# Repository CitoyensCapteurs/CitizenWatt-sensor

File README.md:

CitizenWatt-sensor
==================
Hardware and code running on the sensor for the CitizenWatt project.

For the sensor, install some libs first :
- RF24: https://github.com/stanleyseow/RF24/tree/2a1a4e6e27056844a3bc419d65b8a2d4e0f1770e
- EmonLib: https://github.com/openenergymonitor/EmonLib
- AESLib: https://github.com/DavyLandman/AESLib

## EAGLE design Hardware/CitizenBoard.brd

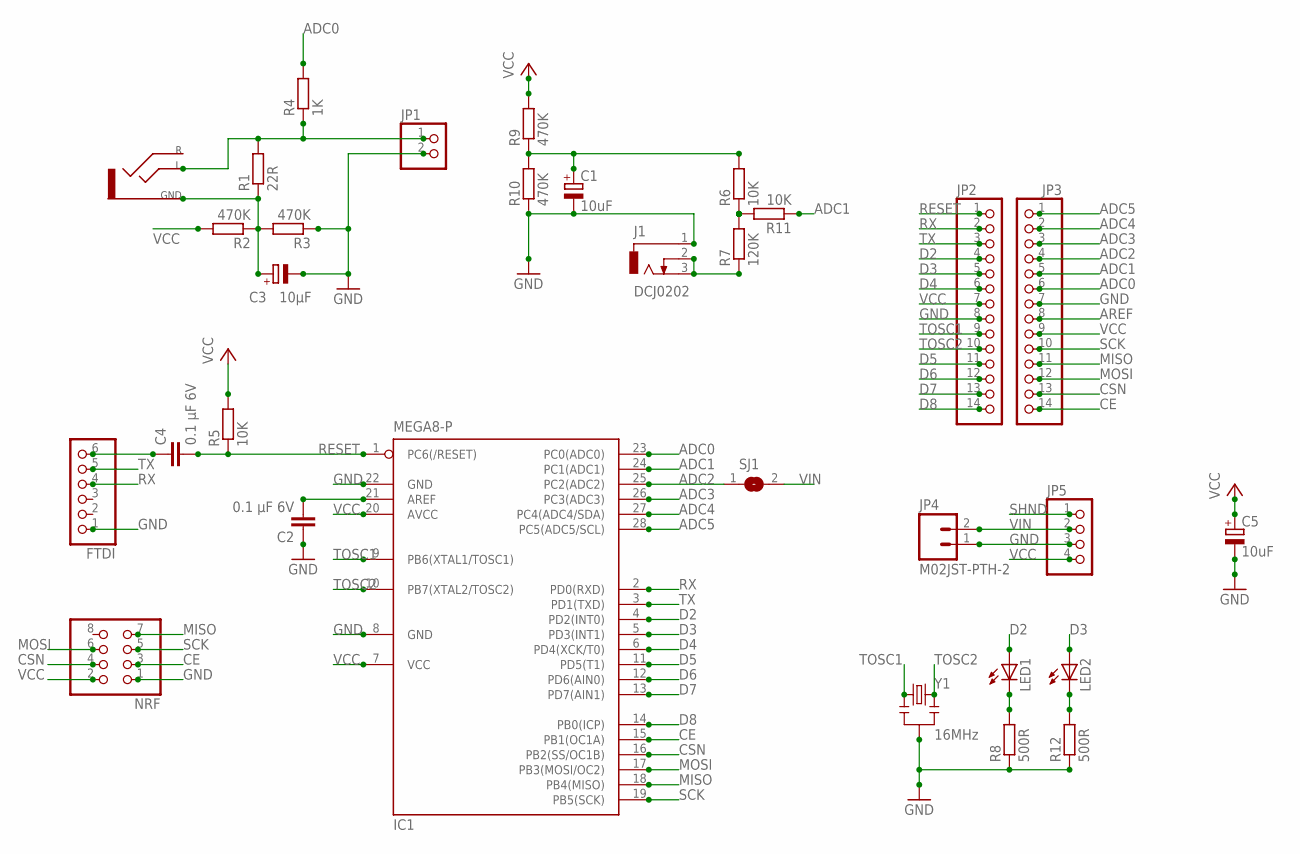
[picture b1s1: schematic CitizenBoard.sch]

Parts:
C1, C5: 10uF; E2,5-6E
C2, C4: 0.1 µF 6V; C025-024X044
C3: 10µF; E2,5-6E
FTDI: PINHD-1X6; 1X06
IC1: MEGA8-P; DIL28-3
J1: DCJ0202
J2: AUDIO-JACK-3.5
JP1: PINHD-1X2; 1X02
JP2, JP3: PINHD-1X14; 1X14
JP4: M02JST-PTH-2; JST-2-PTH
JP5: PINHD-1X4; 1X04
LED1, LED2: LED3MM
NRF: PINHD-2X4; 2X04
R1: 22R; 0204/7
R2, R3, R9, R10: 470K; 0204/7
R4: 1K; 0204/7
R5, R6, R11: 10K; 0204/7
R7: 120K; 0204/7
R8, R12: 500R; 0204/7
SJ1: SJ
Y1: 16MHz; RESONATOR-PTH

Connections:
ADC0: IC1.23 (PC0(ADC0)), JP3.6, R4.2
ADC1: IC1.24 (PC1(ADC1)), JP3.5, R11.1
ADC2: IC1.25 (PC2(ADC2)), JP3.4, SJ1.1
ADC3: IC1.26 (PC3(ADC3)), JP3.3
ADC4: IC1.27 (PC4(ADC4/SDA)), JP3.2
ADC5: IC1.28 (PC5(ADC5/SCL)), JP3.1
AREF: C2.2, IC1.21 (AREF), JP3.8
CE: IC1.15 (PB1(OC1A)), JP3.14, NRF.3
CSN: IC1.16 (PB2(SS/OC1B)), JP3.13, NRF.4
D2: IC1.4 (PD2(INT0)), JP2.4, LED1.A
D3: IC1.5 (PD3(INT1)), JP2.5, LED2.A
D4: IC1.6 (PD4(XCK/T0)), JP2.6
D5: IC1.11 (PD5(T1)), JP2.11
D6: IC1.12 (PD6(AIN0)), JP2.12
D7: IC1.13 (PD7(AIN1)), JP2.13
D8: IC1.14 (PB0(ICP)), JP2.14
GND: C1.-, C2.1, C3.-, C5.-, FTDI.1, IC1.8 (GND), IC1.22 (GND), J1.1, JP1.2, JP2.8, JP3.7, JP4.1, JP5.3, NRF.1, R3.1, R8.1, R10.1, R12.1, Y1.2
MISO: IC1.18 (PB4(MISO)), JP3.11, NRF.7
MOSI: IC1.17 (PB3(MOSI/OC2)), JP3.12, NRF.6
N: J2.5T (L), JP1.1, R1.2, R4.1
unnamed: R6.1, R7.2, R11.2
unnamed: LED2.K (C), R12.2
unnamed: C4.1, FTDI.6
unnamed: C3.+, J2.1S (GND), R1.1, R2.1, R3.2
unnamed: LED1.K (C), R8.2
unnamed: J1.2, J1.3, R7.1
unnamed: C1.+, R6.2, R9.1, R10.2
RESET: C4.2, IC1.1 (PC6(/RESET)), JP2.1, R5.1
RX: FTDI.4, IC1.2 (PD0(RXD)), JP2.2
SCK: IC1.19 (PB5(SCK)), JP3.10, NRF.5
SHND: JP5.1
TOSC1: IC1.9 (PB6(XTAL1/TOSC1)), JP2.9, Y1.1
TOSC2: IC1.10 (PB7(XTAL2/TOSC2)), JP2.10, Y1.3
TX: FTDI.5, IC1.3 (PD1(TXD)), JP2.3
VCC: C5.+, IC1.7 (VCC), IC1.20 (AVCC), JP2.7, JP3.9, JP5.4, NRF.2, R2.2, R5.2, R9.2
VIN: JP4.2, JP5.2, SJ1.2

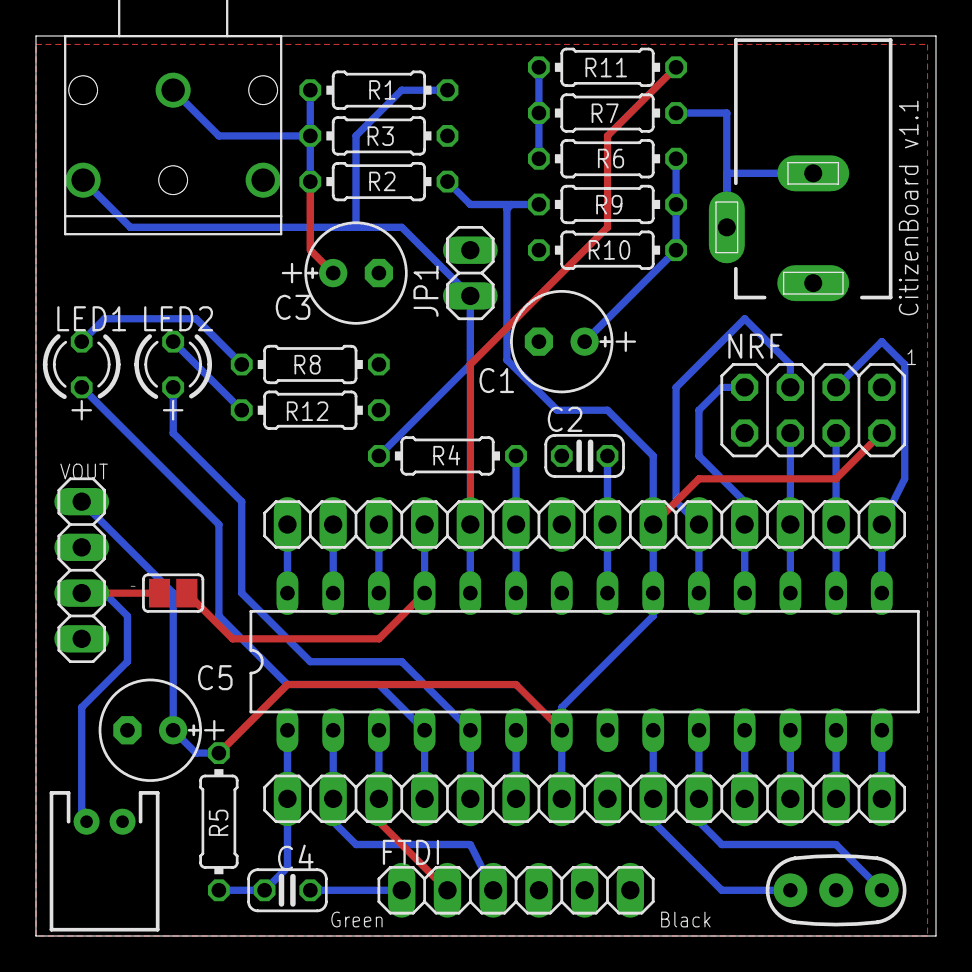
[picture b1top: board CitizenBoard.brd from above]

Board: 2 copper layers, 50.0 x 50.0 mm, 31 parts (0 on the bottom side), 35 nets.

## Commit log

2014-05-11 Beginning of code
2014-05-11 Major functions added
2014-05-11 nRF config
2014-05-11 Voltage measurement should be ok
    TODO : Intensity measurement + nRF sending
2014-05-12 nRF code should be there.
    TODO: power down + check readI code
2014-05-12 Beginning of suspend code
2014-05-12 Code ok, powerdown resets…
2014-05-12 cast problem solved with dBm
2014-05-12 Some bugs left. Main code is here
2014-05-13 Base code for RaspberryPi
2014-05-13 Refactor + TODO cleared
2014-05-15 Moving directories
2014-05-15 eagle files
2014-05-16 Board silk fix
2014-05-18 Silk bottom
2014-05-19 Added TODO
2014-05-20 v1.0 sent for printing, after minor update
2014-06-14 receive updated
2014-06-28 Code used for demo on the 14/06 @ Fabelier
2014-06-28 Clement's code for the sensor
2014-06-28 Fix memory usage
    * Fix memory usage putting strings in flash memory
    * Small refactoring
    * Added automatic startup after 30s
2014-06-28 Updated demo code
2014-07-02 Révision du menu
    Le menu a été modifié
    Le chargement des paramètres également
    But : pouvoir mettre la valeur souhaitée, et non des paramètres
    prédéfinis
    Problème : plantages
2014-07-02 Fixed some bugs with serial baudrate overflow + declaration in switch
2014-07-02 Should be working, need to fix the sleep
2014-07-11 .gitignore pour Eagle
2014-07-11 Renommage des fichiers
2014-07-11 Divers corrections de placement
    Déplacement vers le haut de R1, R2, R3 et C3, pour les éloigner de R8.
    Marquage de la polarisation des diodes et des condensateurs sur le silk.
    Décalage du connecteur FTDI pour ne pas entrer en collision avec NRF
    Décalage de C1 pour la même raison
2014-07-11 Correction de l'empreinte du jack
    Et modification de tracés pour le champ de masse
2014-07-20 Mesure de la valeur de la batterie
    via un solder pad
2014-09-11 Add LED support
2014-09-15 LED Pin and sleep fix
    Red and green pin inverted
    Set the sleep (8 sec)
    Tried the battery measurement (failed)
2014-09-20 Sleep mode, NRF com and EmonLib
    Sleep mode is now working
    Now using EmonLib instead of a copy of their functions
    Serial Baudrate is now fixed to 57600
    Renamed nrf.intensity to nrf.power
    Battery monitoring is now working
    Improved NRF debug
2014-09-22 Fix pin number
2014-09-24 Add AES
2014-10-04 Payload size to 16 Bytes
2014-10-20 Removed menu
2014-10-23 Fix variable ICAL
2014-10-23 CitizenWatt mean ICAL
2014-11-06 Removed outdated receive.cpp
    File moved to Citizenwatt-Base repository
2014-11-06 Modified RF24 lib path
2014-12-13 Switched to 250K by default
    to improve reliability.

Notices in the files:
parts and their libraries:
SparkFun-FreqCtrl: Licensing: Creative Commons ShareAlike 4.0 International - https://creativecommons.org/licenses/by-sa/4.0
